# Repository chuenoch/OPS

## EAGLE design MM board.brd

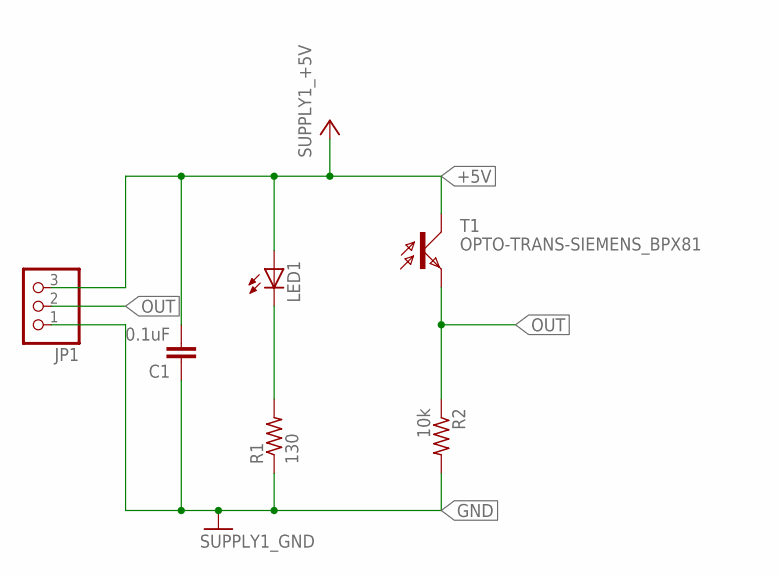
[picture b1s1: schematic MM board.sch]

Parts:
C1: 0.1uF; RCL_C1206
JP1: PINHEAD_PINHD-1X3; PINHEAD_1X03
LED1: LED_LED5MM
R1: 130; RCL_R1206
R2: 10k; RCL_R1206
T1: OPTO-TRANS-SIEMENS_BPX81

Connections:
+5V: C1.2, JP1.3, LED1.A, T1.C
GND: C1.1, JP1.1, R1.1, R2.2
unnamed: LED1.K (C), R1.2
OUT: JP1.2, R2.1, T1.E

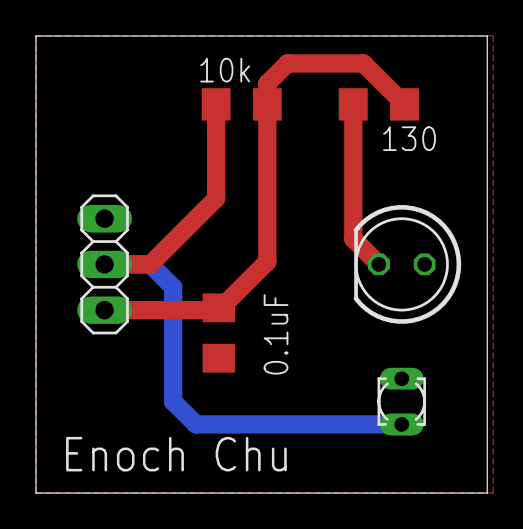
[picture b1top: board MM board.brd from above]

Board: 2 copper layers, 25.1 x 25.4 mm, 6 parts (0 on the bottom side), 4 nets.

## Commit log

2020-04-02 Rename onewallpid2.ino to onewallpid.ino
